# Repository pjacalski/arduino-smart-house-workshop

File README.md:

# Arduino smart house
Arduino workshop I conducted for science club Telephoners at AGH, Cracow. The main purpose for the participants of this workshop was to learn more about microcontrolers and different sensors. The goal set for the end of it was to create a simple home automation system.

##Description
The workshop consisted of a series of meetings, focused on interacting with different sensors, such as:
 - BMP180 and BME280 pressure and temperature sensors
 - DS18B20 temperature sensor
 - PIR movement sensor
 - IR reciever
 - RFID reader

By the end of the workshop the group has prepared software for main board and alarm system. The main board could measure temperature, humidity and atmosferic pressure, and drive 8 channels of relays using remote controller and port expander, while the alarm had three zones guarded by PIR sensors and reed switches, and could be armed and disarmed using RFID card.

A modified version of the main board (with different display and auto-brightness control using LDR) servs as weather station in my dorm room.

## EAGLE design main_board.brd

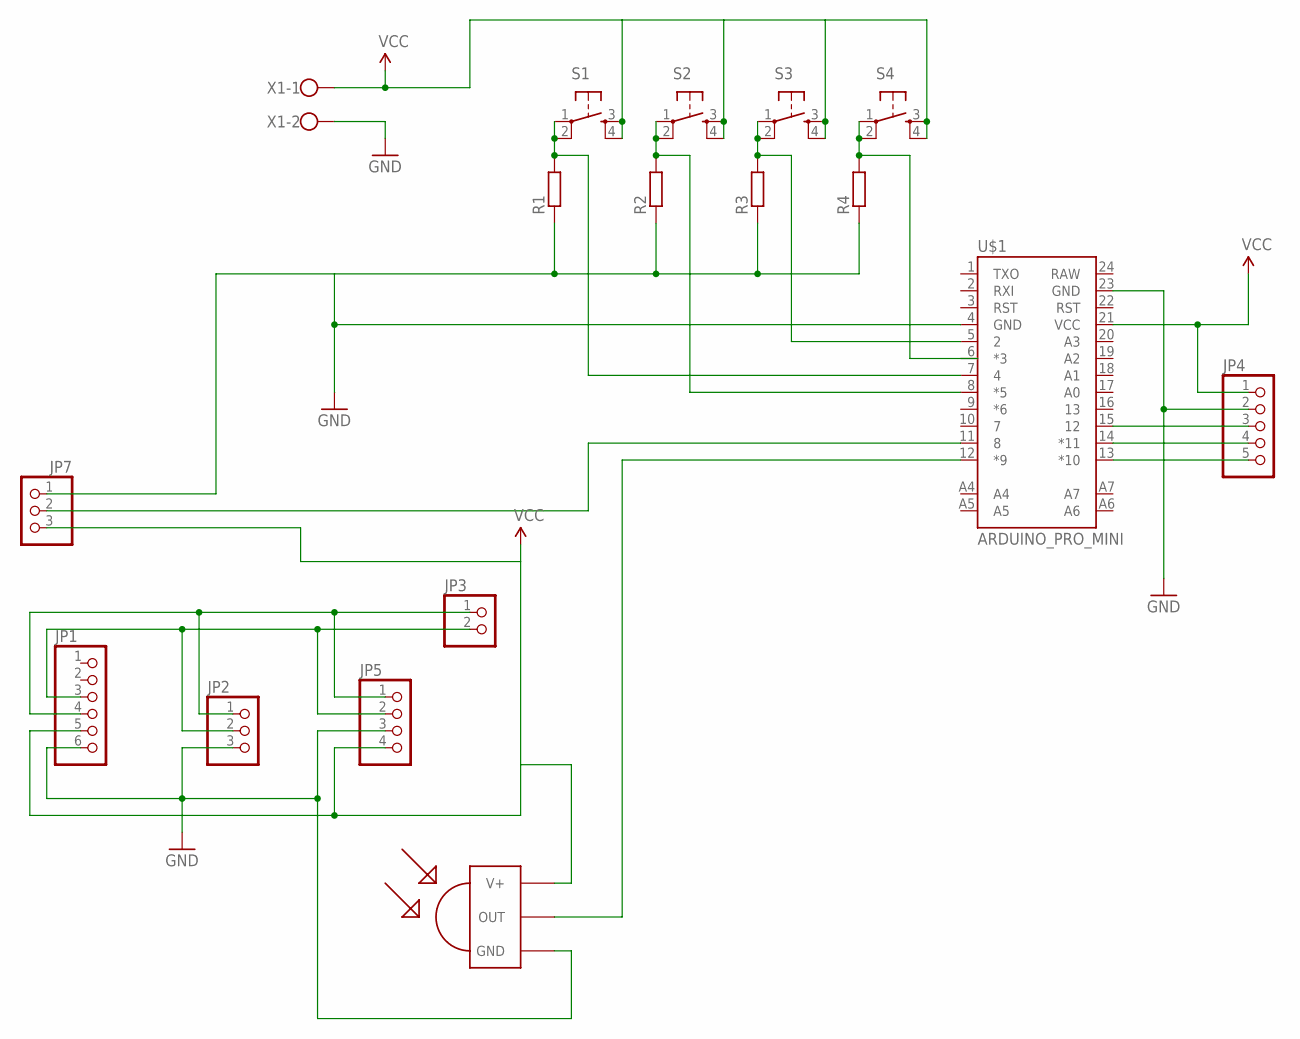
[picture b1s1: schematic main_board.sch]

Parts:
JP1: PINHD-1X6; 1X06
JP2, JP7: PINHD-1X3; 1X03
JP3: PINHD-1X2; 1X02
JP4: PINHD-1X5; 1X05
JP5: PINHD-1X4; 1X04
R1, R2, R3, R4: R0207/10; 0207/10
S1, S2, S3, S4: TAC_SWITCHPTH; TACTILE-PTH
U$1: ARDUINO_PRO_MINI
U$2: TSOP1736; TSOP17XX
X1: W237-102

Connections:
GND: JP1.6, JP2.3, JP4.2, JP5.3, JP7.1, R1.1, R2.1, R3.1, R4.1, U$1.4 (GND), U$1.23 (GND), U$2.GND, X1.2
unnamed: JP4.5, U$1.13 (*10)
unnamed: JP4.4, U$1.14 (*11)
unnamed: JP4.3, U$1.15 (12)
unnamed: U$1.12 (*9), U$2.OUT
unnamed: JP1.4, JP2.1, JP3.1, JP5.1
unnamed: JP1.3, JP2.2, JP3.2, JP5.2
unnamed: JP7.2, U$1.11 (8)
unnamed: R3.2, S3.1, S3.2, U$1.5 (2)
unnamed: R4.2, S4.1, S4.2
unnamed: R2.2, S2.1, S2.2, U$1.8 (*5)
unnamed: R1.2, S1.1, S1.2, U$1.7 (4)
VCC: JP1.5, JP4.1, JP5.4, JP7.3, S1.3, S1.4, S2.3, S2.4, S3.3, S3.4, S4.3, S4.4, U$1.21 (VCC), U$2.V+, X1.1

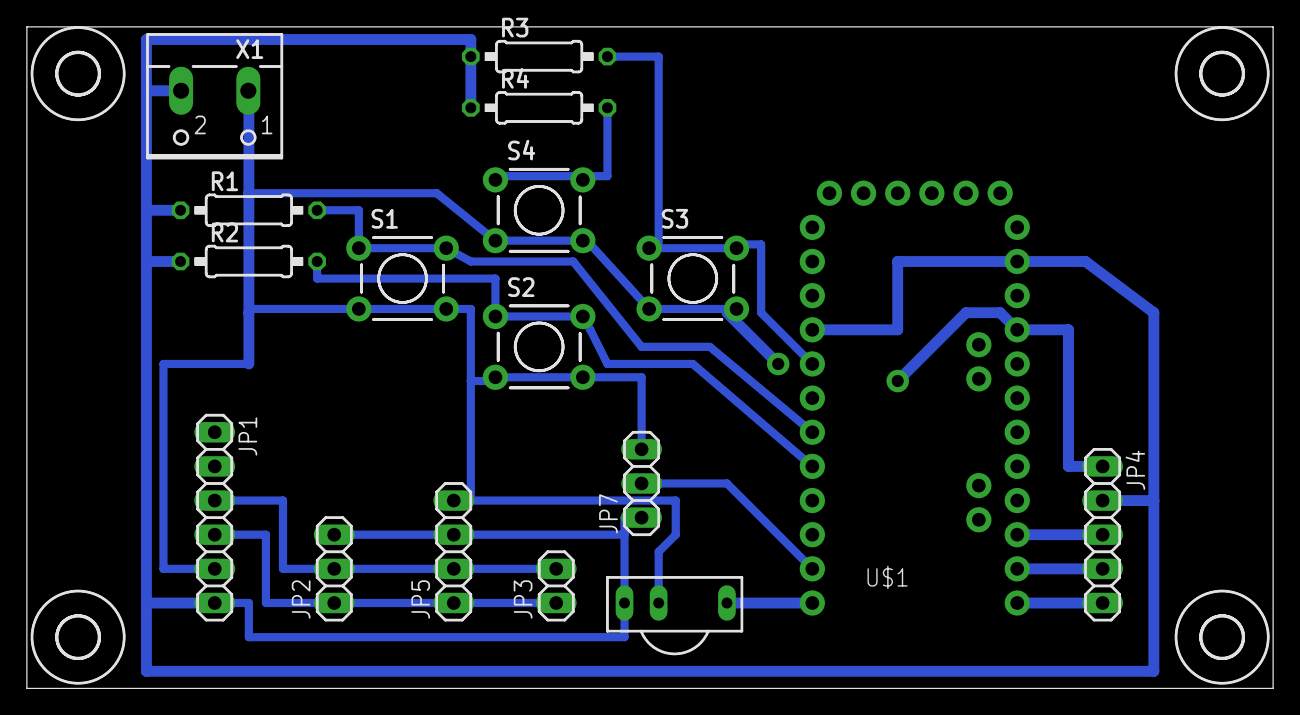
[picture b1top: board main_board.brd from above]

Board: 2 copper layers, 92.7 x 49.2 mm, 21 parts (0 on the bottom side), 13 nets.

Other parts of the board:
U$3, U$4, U$5, U$6: 3,0

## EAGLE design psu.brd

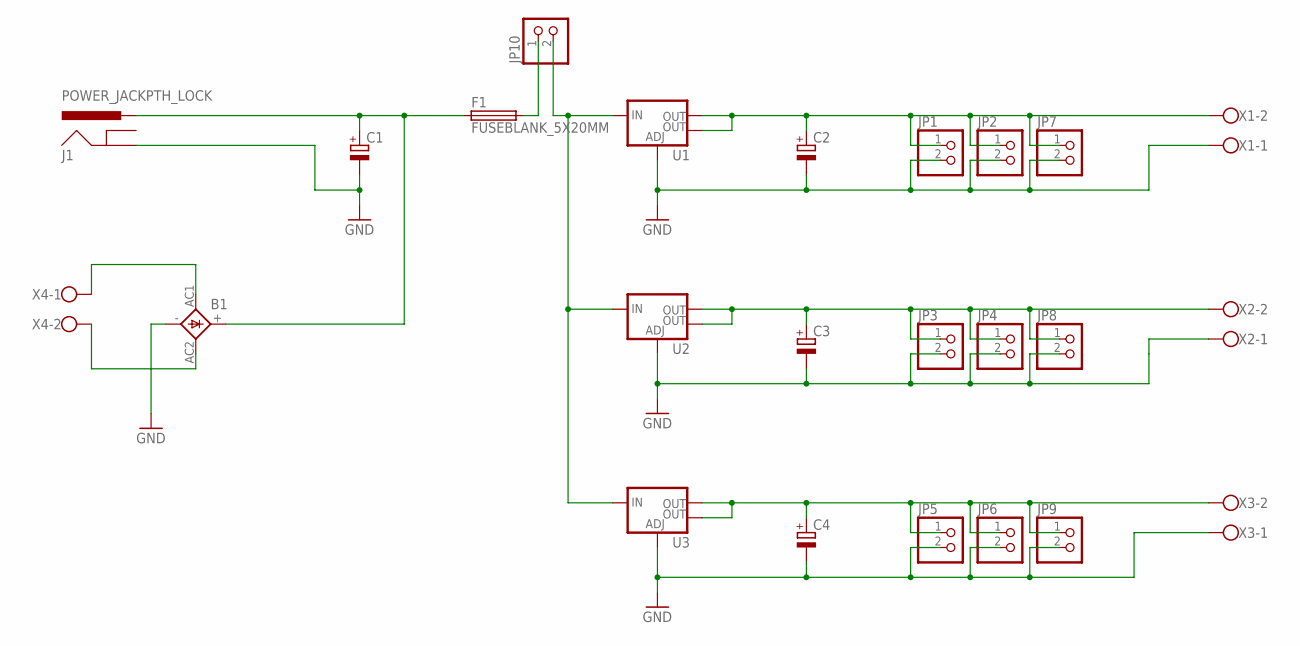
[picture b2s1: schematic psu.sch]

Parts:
B1: KBU
C1: CPOL-EUE5-10.5; E5-10,5
C2, C3, C4: CPOL-EUE2.5-7; E2,5-7
F1: FUSEBLANK_5X20MM; FUSE_HOLDER_5X20MM
J1: POWER_JACKPTH_LOCK; POWER_JACK_PTH_LOCK
JP1, JP2, JP3, JP4, JP5, JP6, JP7, JP8, JP9, JP10: PINHD-1X2; 1X02
U1, U2, U3: V_REG_LM1117SOT223; SOT223
X1, X2, X3, X4: W237-102

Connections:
GND: B1.-, C1.-, C2.-, C3.-, C4.-, J1.GND, JP1.2, JP2.2, JP3.2, JP4.2, JP5.2, JP6.2, JP7.2, JP8.2, JP9.2, U1.1 (ADJ), U2.1 (ADJ), U3.1 (ADJ), X1.1, X2.1, X3.1
unnamed: B1.+, C1.+, F1.1, J1.PWR
unnamed: C2.+, JP1.1, JP2.1, JP7.1, U1.2 (OUT), U1.4 (OUT), X1.2
unnamed: C3.+, JP3.1, JP4.1, JP8.1, U2.2 (OUT), U2.4 (OUT), X2.2
unnamed: C4.+, JP5.1, JP6.1, JP9.1, U3.2 (OUT), U3.4 (OUT), X3.2
unnamed: B1.AC1, X4.1
unnamed: B1.AC2, X4.2
unnamed: JP10.2, U1.3 (IN), U2.3 (IN), U3.3 (IN)
unnamed: F1.2, JP10.1

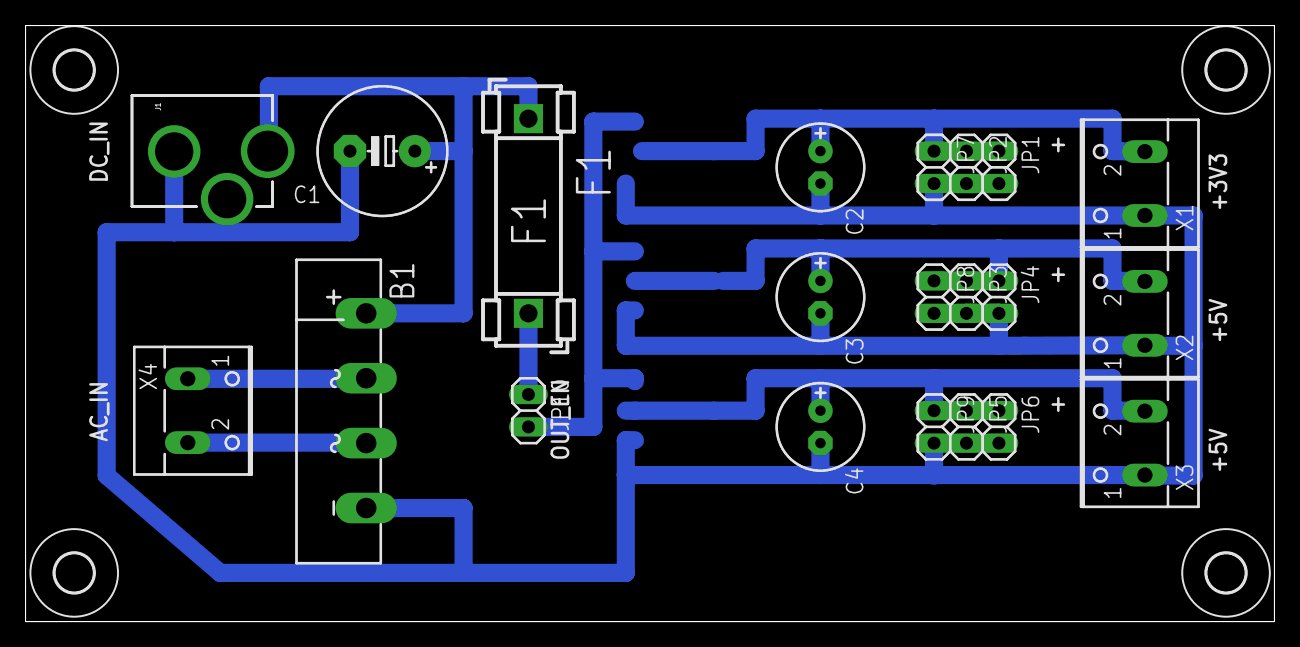
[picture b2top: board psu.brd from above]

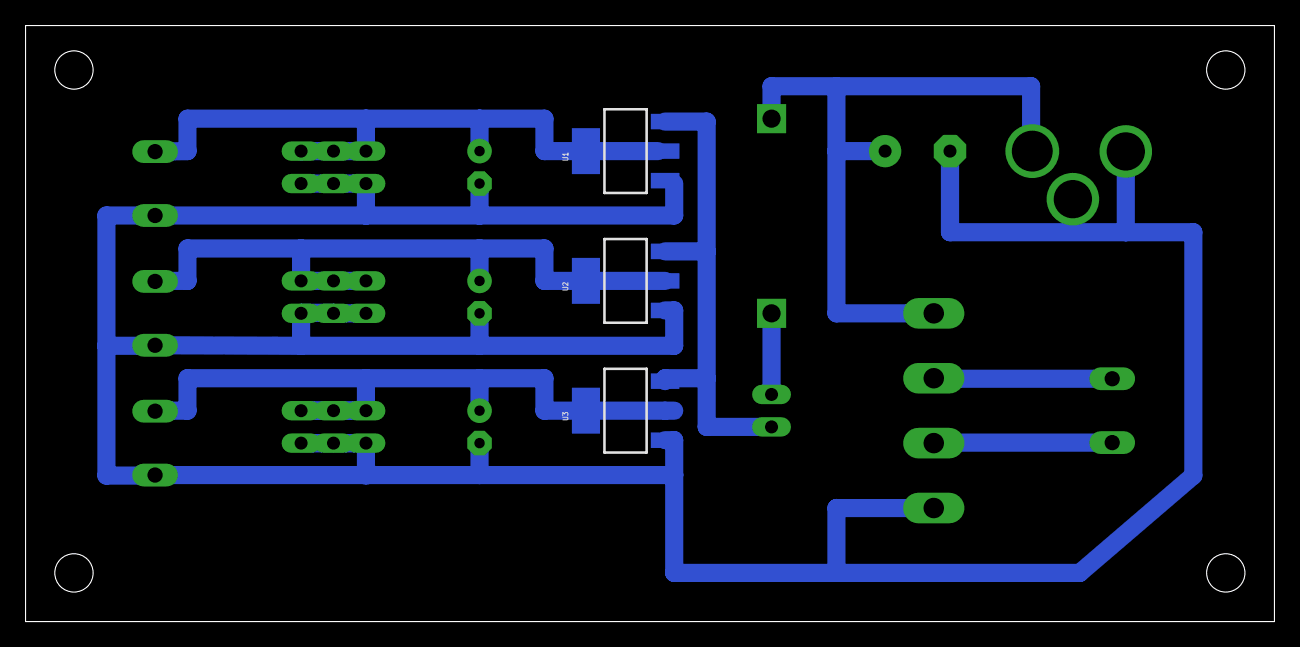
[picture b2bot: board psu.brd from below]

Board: 2 copper layers, 97.8 x 46.7 mm, 28 parts (3 on the bottom side), 9 nets.

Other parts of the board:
U$1, U$2, U$3, U$4: 3,0

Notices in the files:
parts and their libraries:
SparkFun-Boards: Licensing: Creative Commons ShareAlike 4.0 International - https://creativecommons.org/licenses/by-sa/4.0
